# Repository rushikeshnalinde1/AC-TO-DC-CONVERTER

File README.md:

# pcb-projects
pcb projects using kicad

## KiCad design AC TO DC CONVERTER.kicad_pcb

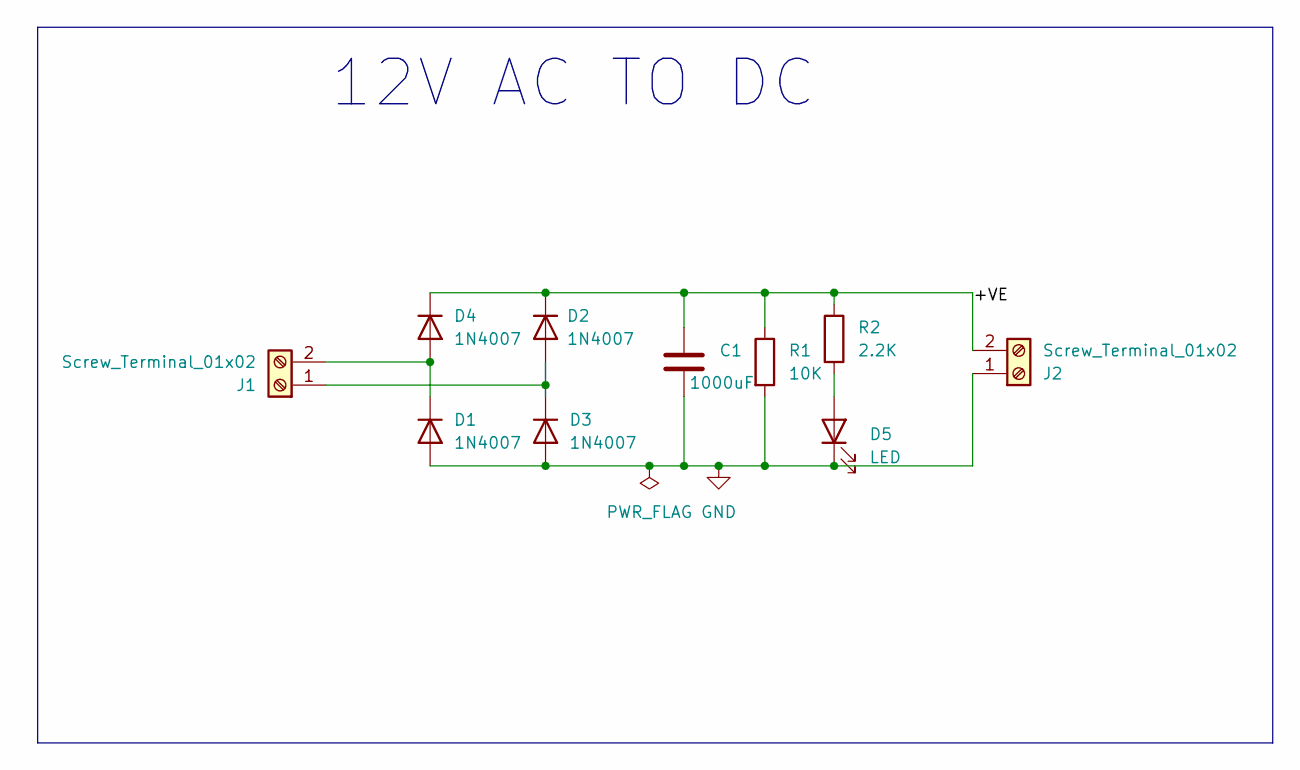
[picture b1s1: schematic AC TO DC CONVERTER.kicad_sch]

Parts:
C1: 1000uF; CP_Radial_D8.0mm_P3.50mm
D1, D2, D3, D4: 1N4007; D_DO-41_SOD81_P10.16mm_Horizontal
D5: LED; LED_D5.0mm
J1, J2: Screw_Terminal_01x02; TerminalBlock_MaiXu_MX126-5.0-02P_1x02_P5.00mm
R1: 10K; R_Axial_DIN0207_L6.3mm_D2.5mm_P7.62mm_Horizontal
R2: 2.2K; R_Axial_DIN0207_L6.3mm_D2.5mm_P7.62mm_Horizontal

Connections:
/+VE: C1.1, D2.1 (K), D4.1 (K), J2.2, R1.1, R2.1
GND: C1.2, D1.2 (A), D3.2 (A), D5.1 (K), J2.1, R1.2
unnamed: D1.1 (K), D4.2 (A), J1.2
unnamed: D2.2 (A), D3.1 (K), J1.1
unnamed: D5.2 (A), R2.2

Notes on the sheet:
12V AC TO DC

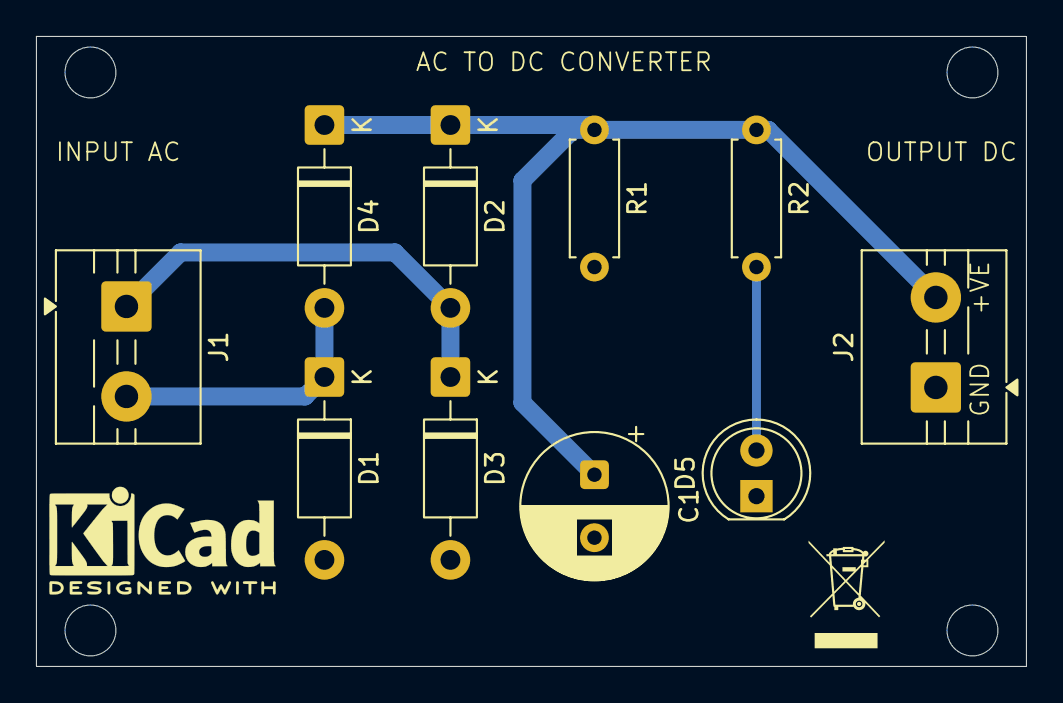
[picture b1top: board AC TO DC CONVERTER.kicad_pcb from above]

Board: 2 copper layers, 55.0 x 35.0 mm, 10 parts (0 on the bottom side), 5 nets.
